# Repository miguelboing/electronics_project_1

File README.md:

# _Electronics Project 1_

This project was created for the discipline EEL7801 - Dept. Electrical and Electronics Engineering.
The **Automatic Pet Feeder** was created to automate the routine of feeding your dog. It's hardware contains
a microcontroller ESP32 responsible for creating a routine of automatic feeding from a user configured time interval.

The firmware project uses the [ESPRESSIF framework](https://www.espressif.com/en/products/modules/esp32)
and all its tools.

## Firmware description

## Hardware description

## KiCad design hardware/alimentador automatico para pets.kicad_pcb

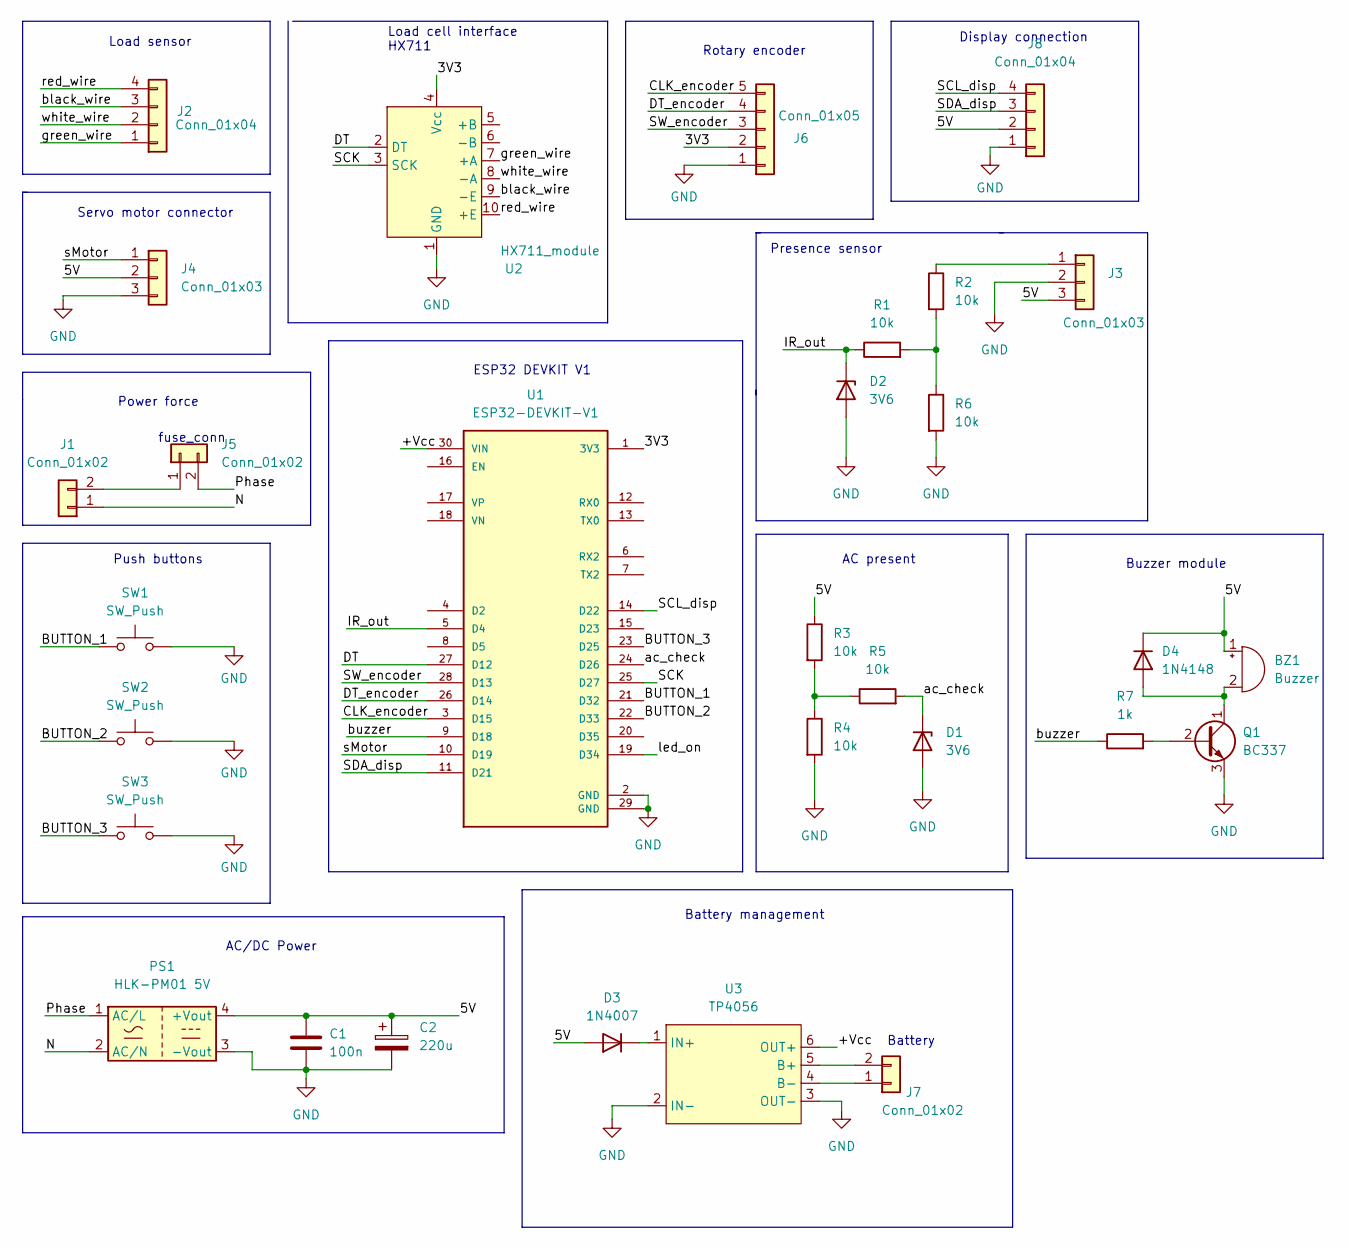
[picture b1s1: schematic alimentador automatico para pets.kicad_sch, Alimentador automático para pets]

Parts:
BZ1: Buzzer; Buzzer_TDK_PS1240P02BT_D12.2mm_H6.5mm
C1: 100n; C_Disc_D6.0mm_W2.5mm_P5.00mm
C2: 220u; CP_Radial_D8.0mm_P2.50mm
D1, D2: 3V6; D_DO-35_SOD27_P7.62mm_Horizontal
D3: 1N4007; D_DO-41_SOD81_P10.16mm_Horizontal
D4: 1N4148; D_DO-35_SOD27_P7.62mm_Horizontal
J1, J7: Conn_01x02; SolderWire-0.1sqmm_1x02_P3.6mm_D0.4mm_OD1mm_Relief
J2: Conn_01x04; SolderWire-0.1sqmm_1x04_P3.6mm_D0.4mm_OD1mm_Relief
J3: Conn_01x03; PinSocket_1x03_P2.54mm_Vertical
J4: Conn_01x03; PinHeader_1x03_P2.54mm_Vertical
J5: Conn_01x02; SolderWire-0.1sqmm_1x02_P3.6mm_D0.4mm_OD1mm
J6: Conn_01x05; PinSocket_1x05_P2.54mm_Vertical
J8: Conn_01x04; PinSocket_1x04_P2.54mm_Vertical
PS1: HLK-PM01 5V; Converter_ACDC_HiLink_HLK-PMxx
Q1: BC337; TO-92L_Inline_Wide
R1, R2, R3, R4, R5, R6: 10k; R_Axial_DIN0207_L6.3mm_D2.5mm_P7.62mm_Horizontal
R7: 1k; R_Axial_DIN0207_L6.3mm_D2.5mm_P7.62mm_Horizontal
SW1, SW2, SW3: SW_Push; SW_PUSH_6mm
U1: ESP32-DEVKIT-V1; MODULE_ESP32_DEVKIT_V1; PARTREV N/A
U2: HX711_module
U3: TP4056

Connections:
/3V3: J6.2, U1.1 (3V3), U2.4 (Vcc)
/5V: BZ1.1 (-), C1.1, C2.1, D3.1 (K), D3.2 (A), D4.1 (K), J3.3, J4.2, J8.2, PS1.4 (+Vout), R3.1, U3.1 (IN+)
/+Vcc: U1.30 (VIN), U3.6 (OUT+)
/BUTTON_1: SW1.1, U1.21 (D32)
/BUTTON_2: SW2.1, U1.22 (D33)
/BUTTON_3: SW3.1, U1.23 (D25)
/CLK_encoder: J6.5, U1.3 (D15)
/DT: U1.27 (D12), U2.2 (DT)
/DT_encoder: J6.4, U1.26 (D14)
/IR_out: D2.1 (K), R1.1, U1.5 (D4)
/N: J1.1, PS1.2 (AC/N)
/Phase: J5.2, PS1.1 (AC/L)
/SCK: U1.25 (D27), U2.3 (SCK)
/SCL_disp: J8.4, U1.14 (D22)
/SDA_disp: J8.3, U1.11 (D21)
/SW_encoder: J6.3, U1.28 (D13)
/ac_check: D1.1 (K), R5.2, U1.24 (D26)
/black_wire: J2.3, U2.9 (-E)
/buzzer: R7.1, U1.9 (D18)
/green_wire: J2.1, U2.7 (+A)
/led_on: U1.19 (D34)
/red_wire: J2.4, U2.10 (+E)
/sMotor: J4.1, U1.10 (D19)
/white_wire: J2.2, U2.8 (-A)
GND: C1.2, C2.2, D1.2 (A), D2.2 (A), J3.2, J4.3, J6.1, J8.1, PS1.3 (-Vout), Q1.3 (E), R4.2, R6.2, SW1.2, SW2.2, SW3.2, U1.2 (GND), U1.29 (GND), U2.1 (GND), U3.2 (IN-), U3.3 (OUT-)
unnamed: BZ1.2 (+), D4.2 (A), Q1.1 (C)
unnamed: J1.2, J5.1
unnamed: J3.1, R2.1
unnamed: J7.1, U3.4 (B-)
unnamed: J7.2, U3.5 (B+)
unnamed: Q1.2 (B), R7.2
unnamed: R1.2, R2.2, R6.1
unnamed: R3.2, R4.1, R5.1

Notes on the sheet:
AC/DC Power
Rotary encoder
Buzzer module
Battery
Load sensor
Presence sensor
Load cell interface HX711
ESP32 DEVKIT V1
Display connection
AC present
Power force
Battery management
Push buttons
fuse_conn
Servo motor connector

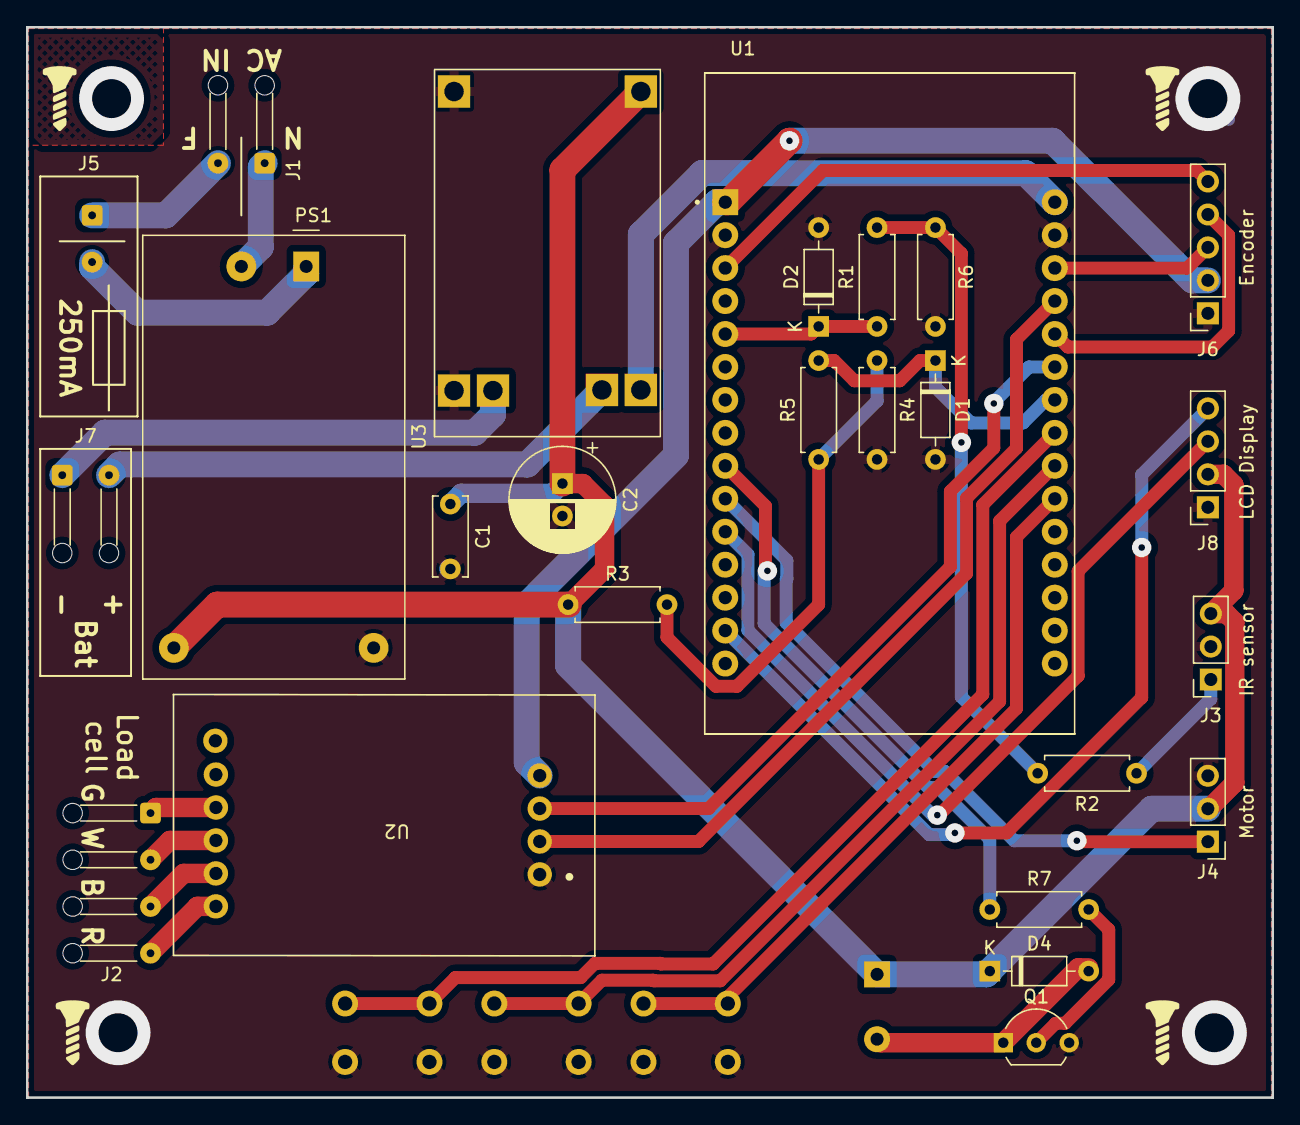
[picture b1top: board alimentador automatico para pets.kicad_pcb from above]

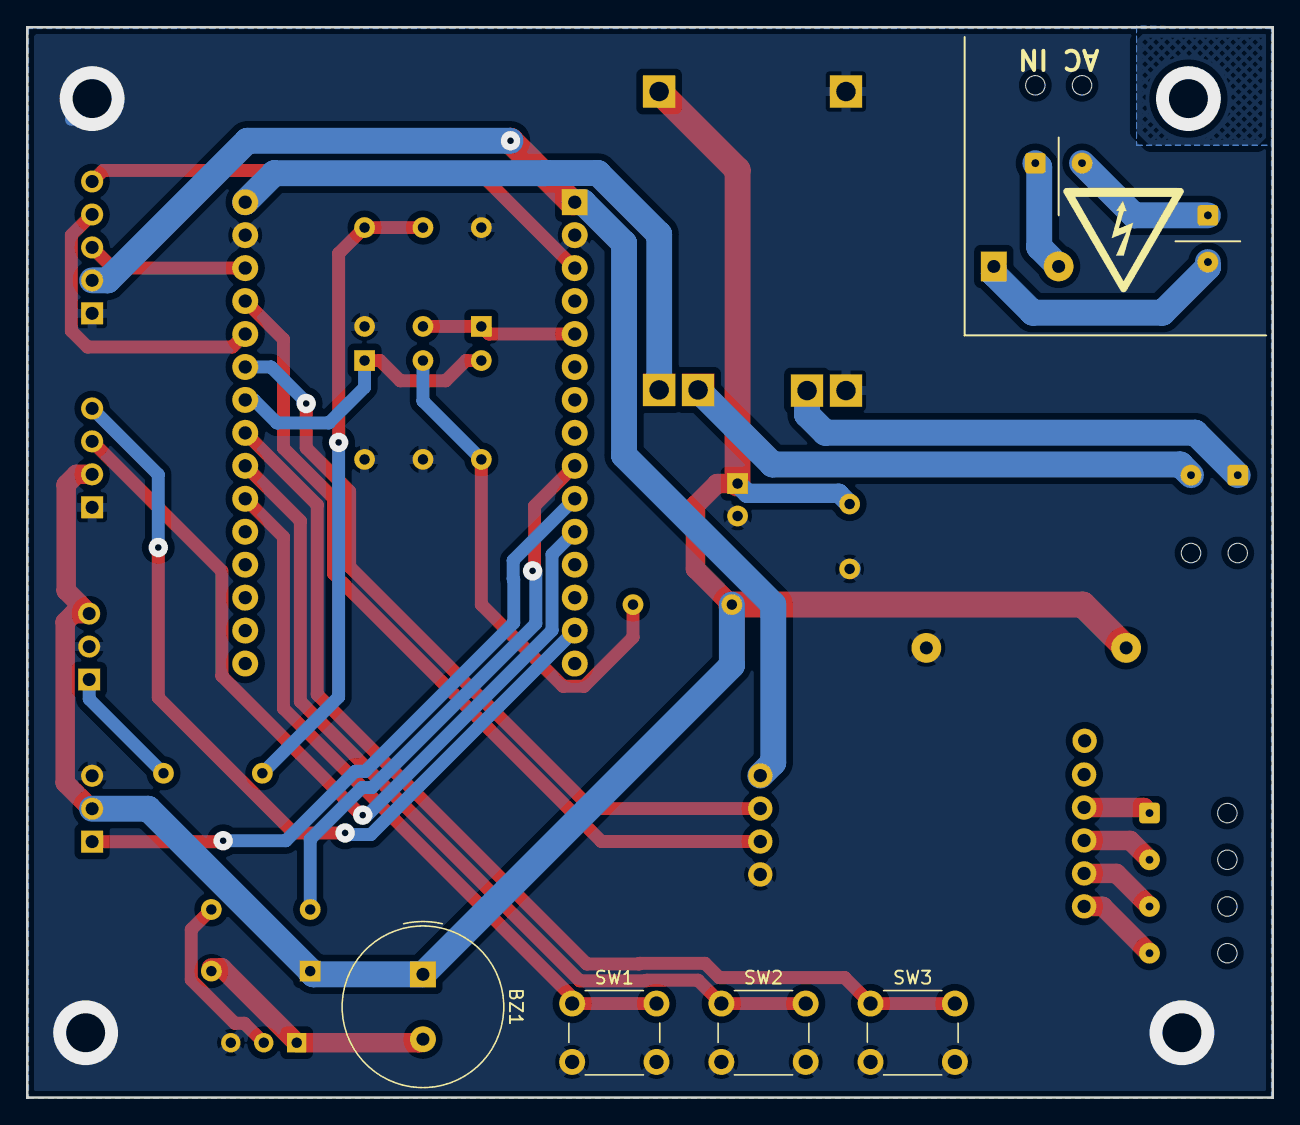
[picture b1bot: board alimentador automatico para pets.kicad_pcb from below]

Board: 2 copper layers, 96.0 x 82.5 mm, 29 parts (4 on the bottom side), 32 nets.

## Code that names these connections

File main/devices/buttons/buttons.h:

/*
 * buttons.h
 *
 *  Created on: 18/05/2022
 *
 */

#ifndef BUTTONS_H_
#define BUTTONS_H_

typedef enum
{
    BUTTON_1 = GPIO_NUM_32,          
    BUTTON_2 = GPIO_NUM_33,            
    BUTTON_3 = GPIO_NUM_25         
} button_e;

void button_init(button_e button);

void button_reset_states(void);

void button_update_state(button_e button);

int button_is_pressed(button_e button);

int button_get_state(button_e button);

#endif /* BUTTONS_H_ */

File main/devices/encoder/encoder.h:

/*
 * encoder.h
 *
 *  Created on: 26/05/2022
 *
 */

#ifndef ENCODER_H_
#define ENCODER_H_

typedef enum
{
    CLK_encoder = GPIO_NUM_15,         
    DT_encoder = GPIO_NUM_14,
    SW_encoder = GPIO_NUM_13,
    CLK_past_state = 1,      
    SW_encoder_feedback = 0,
} encoder_e;

void encoder_init(encoder_e encoder);

void encoder_update_state(encoder_e encoder);

int encoder_verify_level(encoder_e encoder);

int encoder_get_state(encoder_e encoder);

void reset_sw_encoder_state(void);

#endif /* ENCODER_H_ */

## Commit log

2022-05-06 Added sample project
2022-05-08 Adding Esp32 documentation
2022-05-16 Initial hardware files
2022-05-17 Added all symbols closed #3
2022-05-17 schematic organization update
2022-05-17 initial model files
2022-05-17 create model files
2022-05-18 Implementing initial blink led example
2022-05-18 Adding .gitignore
2022-05-18 Adding files to .gitignore #9
2022-05-18 Creating device files
2022-05-19 add reference documentation
2022-05-19 pins with external interrupt
2022-05-19 add push buttons to shcematic
2022-05-19 add references to push buttons and resistors
2022-05-19 Added function definitions for buttons #4
2022-05-19 initial modeling files
2022-05-20 Proximity sensor function declarations and definitions #8
2022-05-20 Working functions for proximity sensor resolves #8
2022-05-21 Modified presence sensor pin and voltage closed #15
2022-05-22 Comittando a funcao feita para os buttons (há um exemplo de funcionamento no main.c)
2022-05-22 Update main.c
    Corrigindo indentação
2022-05-22 Update buttons.c
    Corrigindo indentação
2022-05-24 closes #4
2022-05-24 change labels and pins for buttons closed #17
2022-05-25 introduction to technical drawing
2022-05-25 add new theme in kicad vizualization
2022-05-25 Adding initial project description to README
2022-05-26 rearrange schematic
2022-05-27 Including IoT lib to handle servo motor #6
2022-05-27 Servo motor device resolves #6
2022-05-30 closes #2, closes #4; Working functions for buttons and encoder
2022-06-01 pcb design start
2022-06-02 removing leds and changing components positions #14
2022-06-03 add battery module
2022-06-04 att schematic #14
2022-06-04 Updating buttons and encoder functions
2022-06-04 Improving encoder.c indentation
2022-06-04 Adding dependencies.lock to .gitignore #9
2022-06-04 Removing cached untracked files #9
2022-06-07 Creating RTC device #5
2022-06-07 added buzzer #21
2022-06-08 add 3d models pins #14
2022-06-09 place components and board roadmap #22
2022-06-09 pcb design review
2022-06-23 add gerber files closed #22
2022-06-23 update step export
2022-06-23 mechanical design system #13
2022-07-05 Adding load sensor lib #7
2022-07-08 Adding initial load sensor device without calibration #7
2022-07-08 Adding submodule libraries
2022-07-08 Updating references to libraries in lib directory
2022-07-09 Adding working integrated functions for display, encoder and buttons - closes #1
2022-07-09 Updated encoder_variation_display() since it was not returning any value to the screens functions.
2022-07-09 Upgrading display_go_screen_0_hour() and display_go_screen_0_minutes(), adding esp_log through the whole program for future debug purposes, also added delays because of watchdogs getting triggered
2022-07-09 Adding necessary components to i2c_display funcionality, both components were modified to work in our current esp_idf version
2022-07-10 Working integrated functions for display, buttons, encoder and RTC
2022-07-12 Defining size for auxiliary arrays #1
2022-07-12 Improving code organization #1
2022-07-12 Removing RTC functions from display
2022-07-12 Improvements for RTC
2022-07-13 Adding optimations to code
2022-07-14 Adding RTC absolute time functions
2022-07-15 Creating Debug mode with feeding task
2022-07-15 Implementing ac_check device
2022-07-16 Improving working functions
2022-07-18 Working on bugs
2022-07-27 Adding final version
